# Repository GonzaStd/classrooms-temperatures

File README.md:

> [!IMPORTANT]  
> This project has been made for a specific purpose. If you want to replicate this, you would have to ADAPT IT. However, example code and circuit documentation are provided below on the index, and they are for general use. 

[Here](https://app.cirkitdesigner.com/project/02f16717-05df-46d2-9647-529fff1c8d03) is the url of the circuit.

### Index
* [Circuit Explaination](docs/circuit.md)
* [Example code for general use](docs/example-code.md)

## Context
With the purpose of measuring the temperature of classrooms in our school (and so the thermal discomfort), I've made this project that connects esp-01 modules that act like mqtt clients that publishes temperature and humidity, and by the other side subscribes to a topic they use to know WHEN to send data. 

On the other hand, we'll need a broker, in this case I'll use a Raspberry Pi. This one has to send a request to their clients, receive temperature and humidity, then upload the data to a Google Spreadsheet. 

After a few months, this data will be used to analyse the thermal discomfort and then a request will be sent asking the authorities to allow the placement of rotating fans and curtains (currently there are few fans, they do not rotate and there are no curtains).

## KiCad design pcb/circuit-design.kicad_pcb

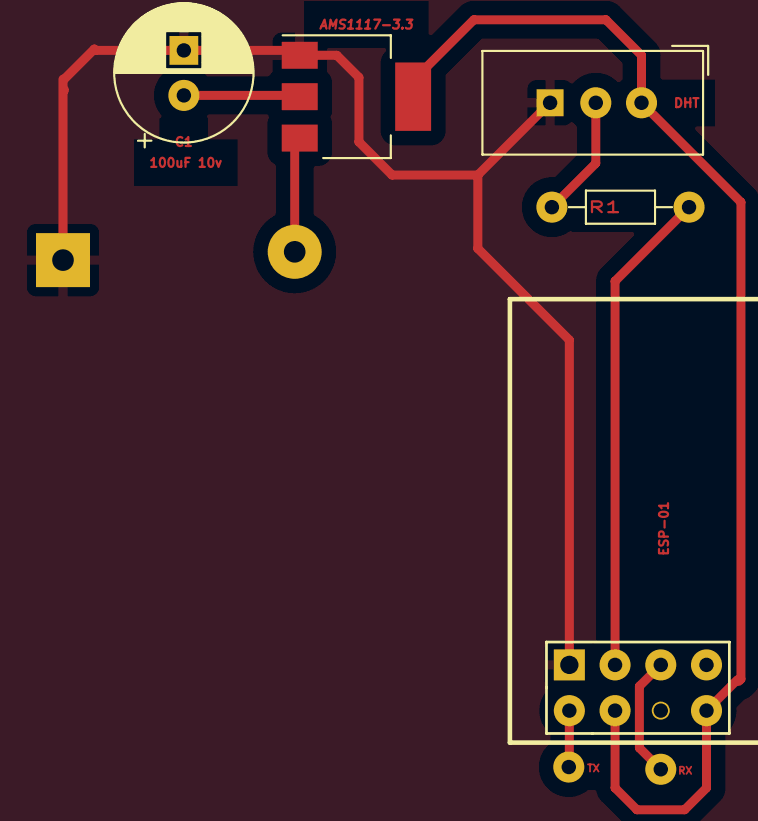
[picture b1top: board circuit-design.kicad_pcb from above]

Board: 2 copper layers, 5 parts (0 on the bottom side), 4 nets.

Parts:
C1: 100uF 10v; CP_Radial_D7.5mm_P2.50mm
DHT: DHT; three_pin_DHT11_5.5x12.0_P2.54mm
R1: 4.7kOhm; R_Axial_DIN0204_L3.6mm_D1.6mm_P7.62mm_Horizontal
U1: ESP-01
U2: AMS1117-3.3; SOT-223-3_TabPin2

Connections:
+3V3: C1.1, DHT.1 (VCC), U1.3 (CH_PD), U1.7 (VCC), U2.2 (VO)
GND: C1.2, DHT.3 (NC), U1.2 (GND), U2.1 (GND)
unnamed: DHT.2 (IO), R1.1
unnamed: R1.2, U1.4 (GPIO2)

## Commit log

2025-10-29 Trying to connect to Public WiFi network portal
2025-11-06 Broker started. It listents to all topics
2025-11-06 Better setup, localhost for broker, wifi connect working and without debugging prints.
2025-11-08 Documentation provided
2025-11-08 mqtt-client sends data when "send" topic sends "read".
2025-11-08 Circuit updated
2025-11-15 PCB ready. I took me 2 hours and 48 minutes
2025-11-17 Fixed something missing and improved a better visibility
2025-12-12 New code without making any probe.
